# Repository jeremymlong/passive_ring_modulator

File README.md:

# Classic passive ring modulator

## Specs
 * 4 HP

## BOM
| Part | Quantity | Link |
|------|------|------|
| Diode (Germanium or Schottky) | 4 | |
| PJ301M or PJ-3001F (Thonkiconn) | 3 | [Tayda](https://www.taydaelectronics.com/pj-3001f-3-5-mm-mono-phone-jack.html) |
| Transformer | 2 | [ebay](https://www.ebay.com/itm/394816880166) |

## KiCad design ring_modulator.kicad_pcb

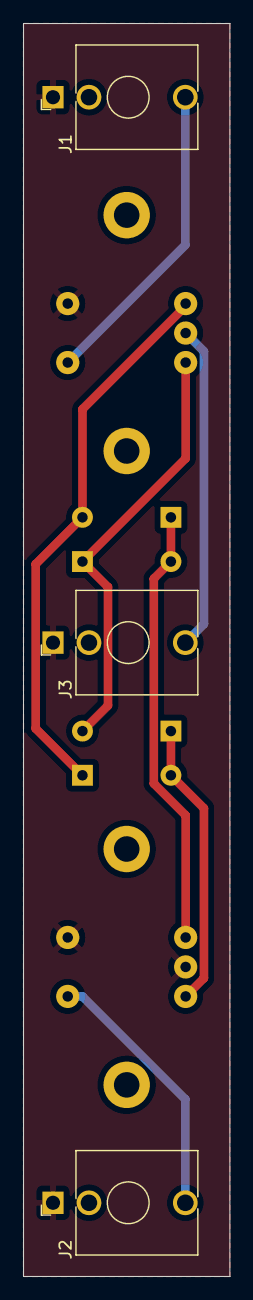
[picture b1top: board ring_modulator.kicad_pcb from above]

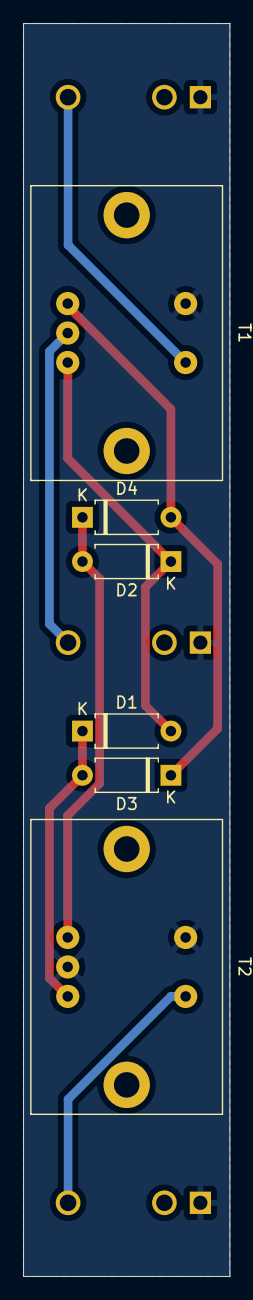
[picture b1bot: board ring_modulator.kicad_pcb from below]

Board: 2 copper layers, 17.8 x 108.0 mm, 9 parts (6 on the bottom side), 8 nets.

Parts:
D1, D2, D3, D4: D; D_A-405_P7.62mm_Horizontal
J1: Input; Jack_3.5mm_QingPu_WQP-PJ398SM_Vertical_CircularHoles
J2: Output; Jack_3.5mm_QingPu_WQP-PJ398SM_Vertical_CircularHoles
J3: Carrier; Jack_3.5mm_QingPu_WQP-PJ398SM_Vertical_CircularHoles
T1, T2: Transformer_1P_SS; audio_transformer

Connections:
GND: J1.S, J2.S, J3.S, T1.2, T2.2, T2.4
unnamed: D1.1, D3.2, T2.5
unnamed: D1.2, D2.1, T1.5
unnamed: D2.2, D4.1, T2.3
unnamed: D3.1, D4.2, T1.3
unnamed: J1.T, T1.1
unnamed: J2.T, T2.1
unnamed: J3.T, T1.4

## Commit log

2024-04-07 Added v0.1 jlc gerbers
